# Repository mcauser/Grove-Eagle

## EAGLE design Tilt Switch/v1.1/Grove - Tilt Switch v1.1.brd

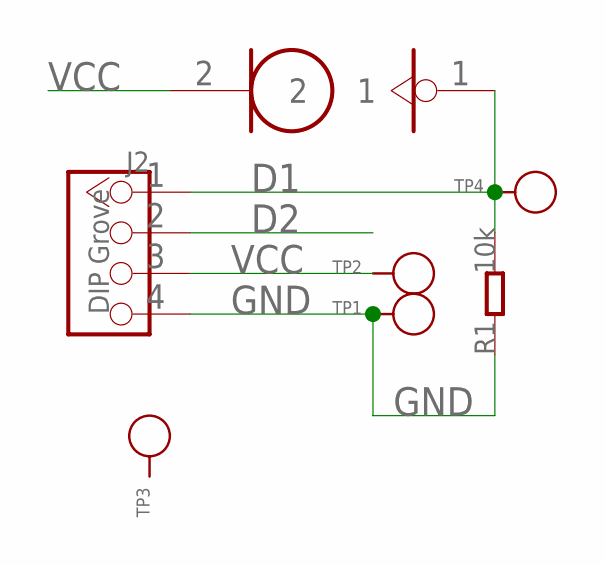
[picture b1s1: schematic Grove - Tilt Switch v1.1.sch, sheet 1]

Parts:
J1: TILT
J2: DIP Grove; 4P-2.0
R1: 10k; 0603
TP1, TP2, TP3, TP4: PAD-TEST-POINT'4545'; TP_4545

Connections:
D1: J1.1, J2.1, R1.2, TP4.T
D2: J2.2
GND: J2.4, R1.1, TP1.T
VCC: J1.2, J2.3, TP2.T

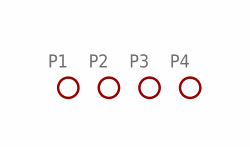
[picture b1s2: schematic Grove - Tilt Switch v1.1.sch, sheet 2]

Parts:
P1, P2, P3, P4: PAD-MARK; ROUND-MARK-1.0

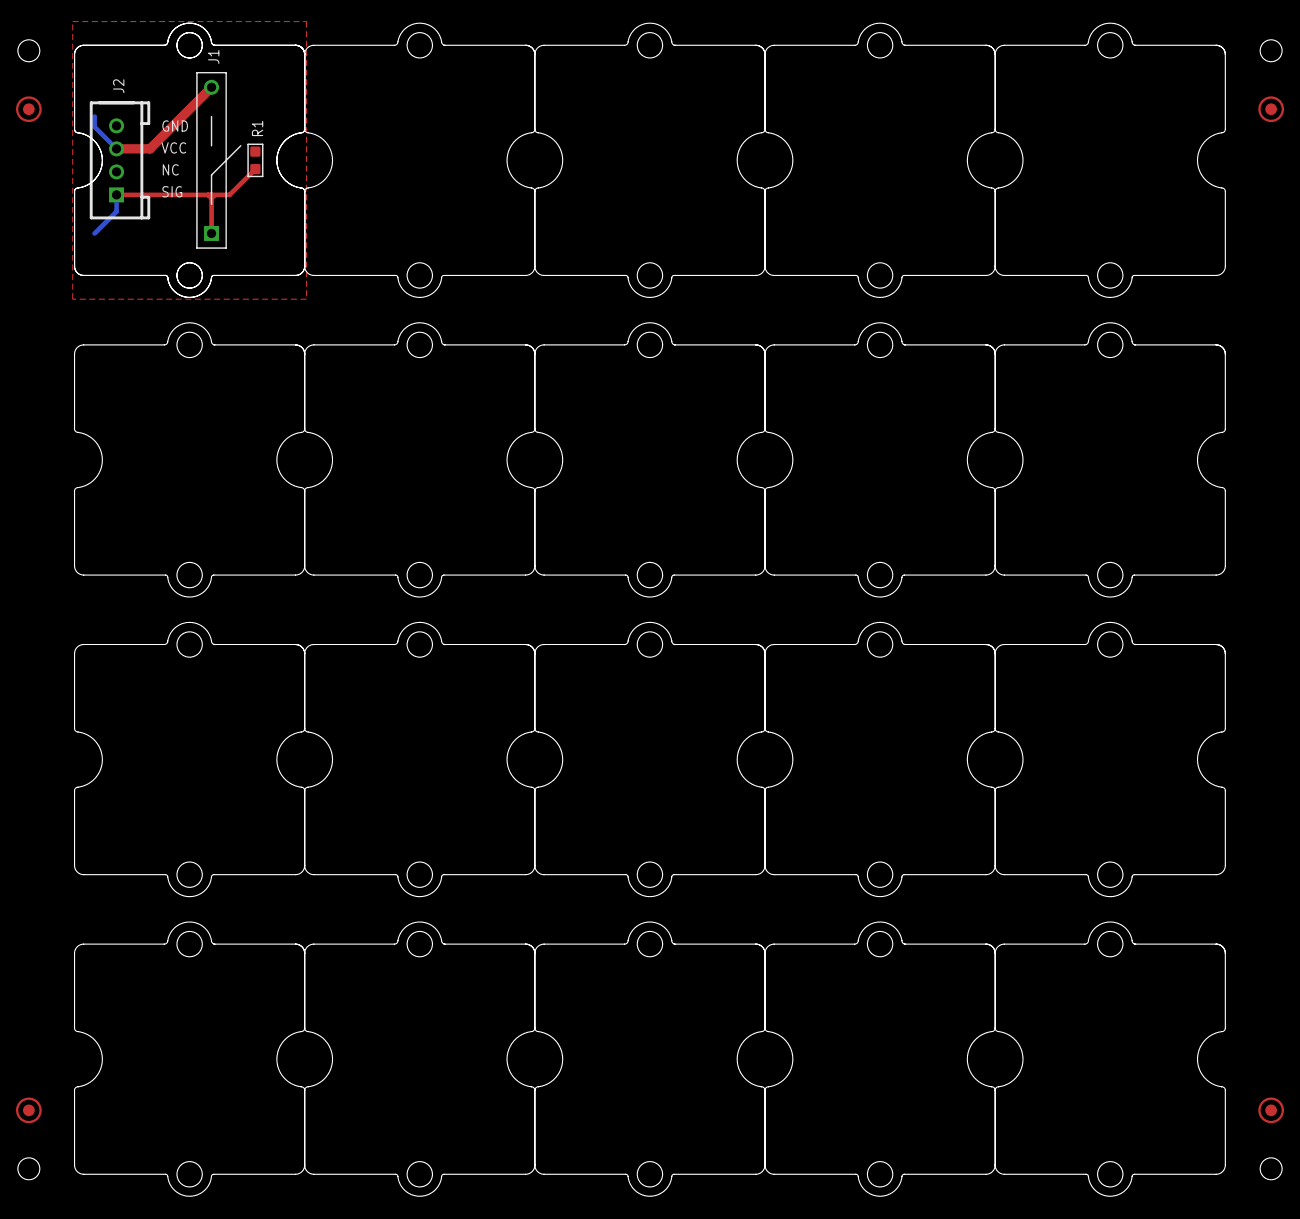
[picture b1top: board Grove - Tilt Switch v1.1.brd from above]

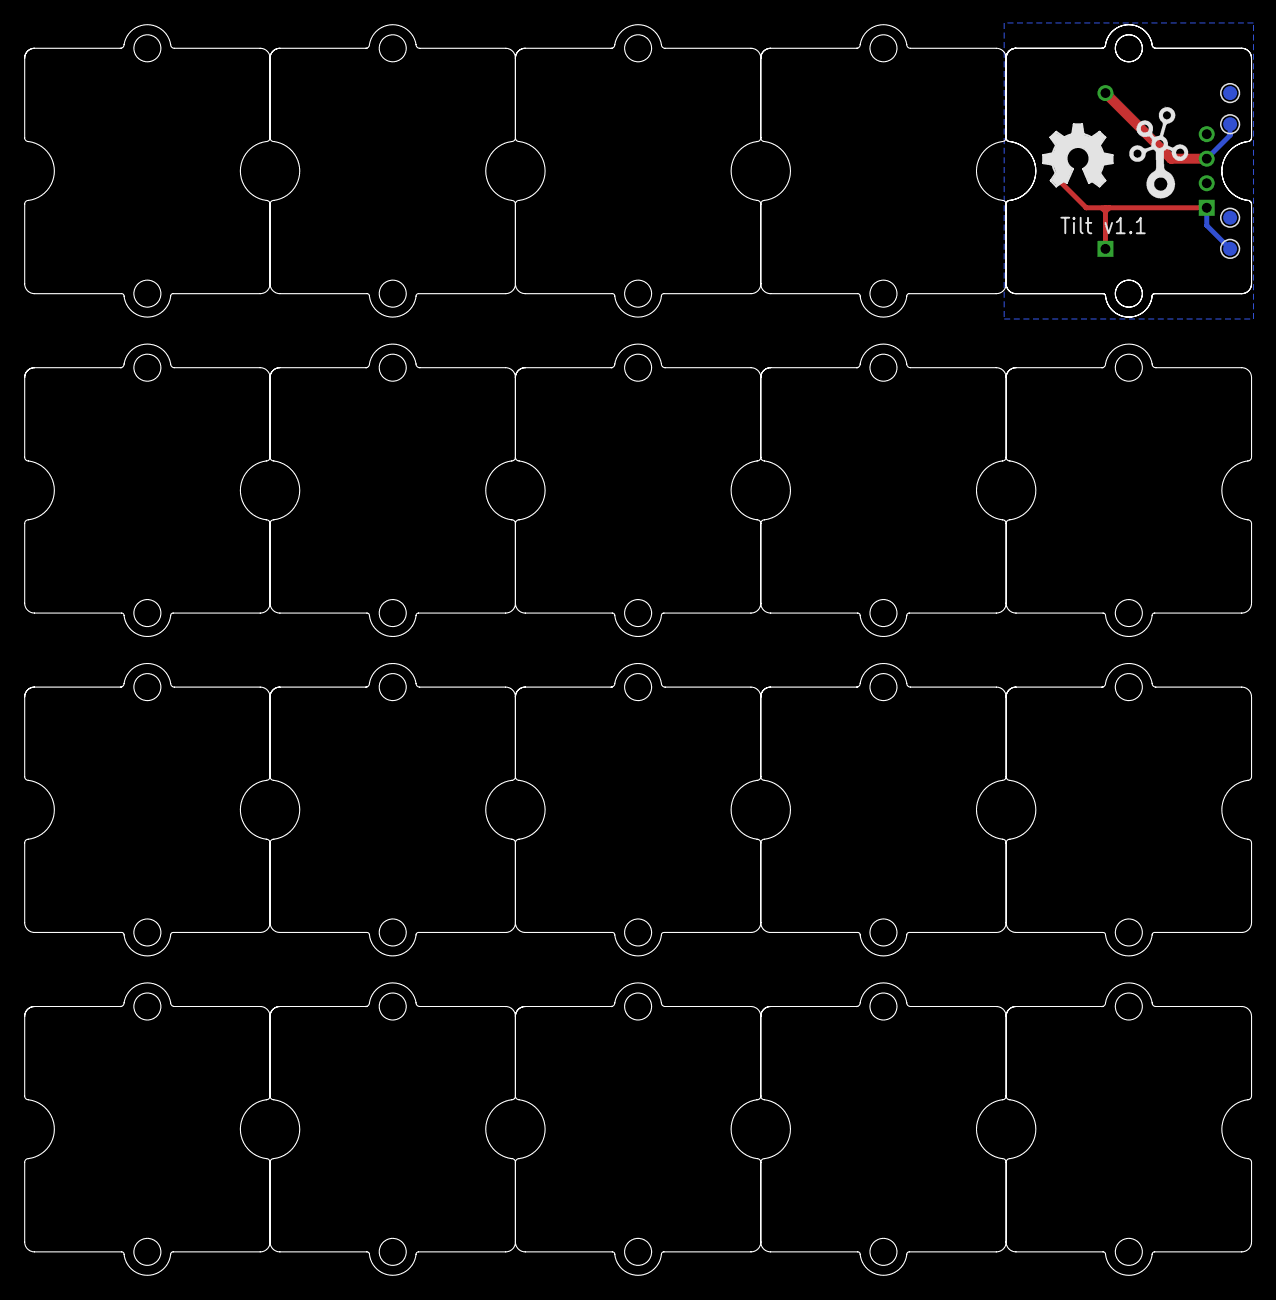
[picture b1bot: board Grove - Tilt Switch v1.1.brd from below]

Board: 2 copper layers, 100.0 x 101.9 mm, 34 parts (6 on the bottom side), 3 nets.

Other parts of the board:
U$2, U$6, U$7, U$8, U$9, U$10, U$11, U$12, U$13, U$14, U$15, U$16, U$17, U$18, U$19, U$20, U$21, U$22, U$23, U$24, U$25: 1U-DIM-W/-DRILL
U$3: OSHW_FILLX200_NOTEXT
U$5: TWIGLOGO

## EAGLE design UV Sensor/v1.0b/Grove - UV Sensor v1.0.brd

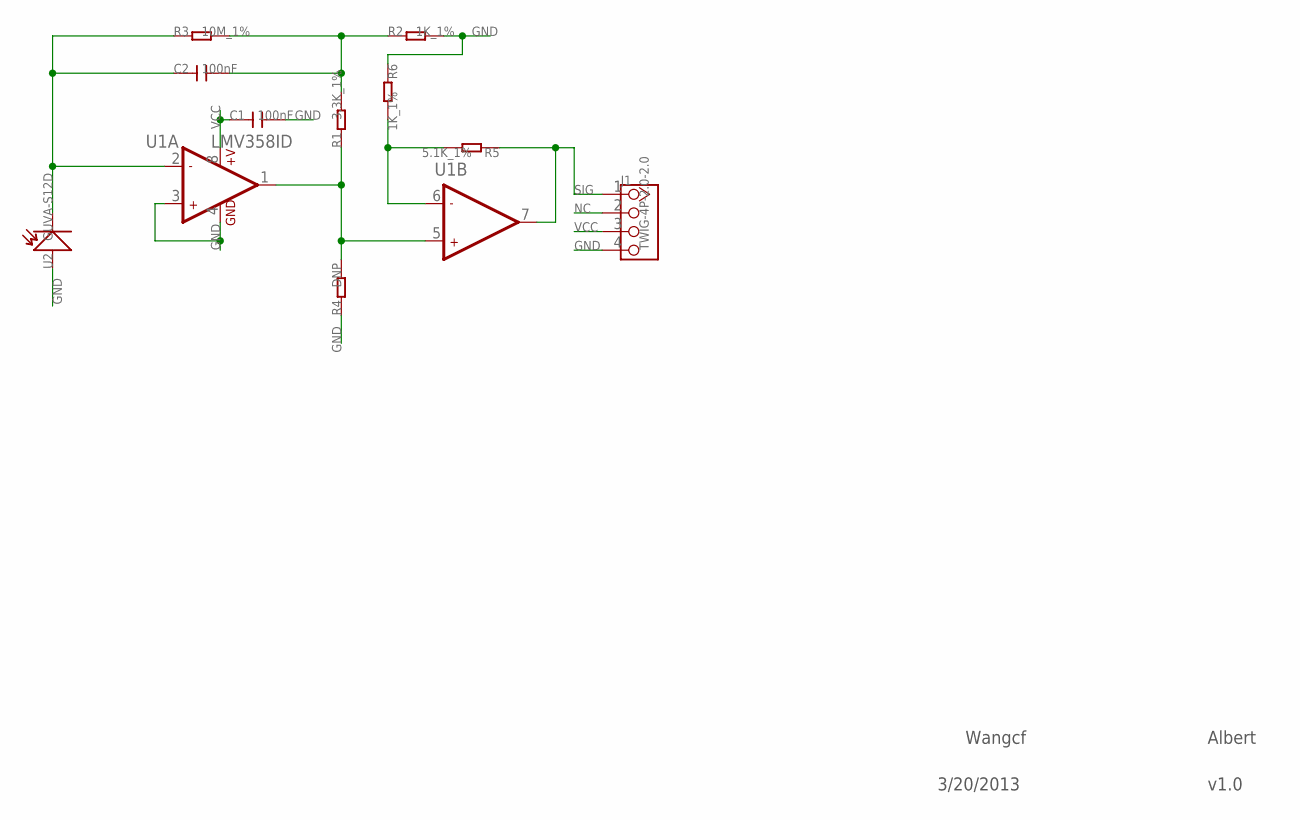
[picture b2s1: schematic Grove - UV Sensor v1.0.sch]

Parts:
C1, C2: 100nF; C0603
J1: TWIG-4P-2.0-2.0; 4P-2.0
R1: 3.3K_1%; R0603
R2, R6: 1K_1%; R0603
R3: 10M_1%; R0603
R4: DNP; R0603
R5: 5.1K_1%; R0603
U1: LMV358ID; SO08
U2: GUVA-S12D; LED-3528

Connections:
GND: C1.2, J1.4, R2.2, R4.1, R6.1, U1.3 (+IN1), U1.4 (GND), U2.1 (+)
unnamed: C2.1, R3.1, U1.2 (-IN1), U2.2 (-)
unnamed: R5.2, R6.2, U1.6 (-IN2)
unnamed: C2.2, R1.2, R2.1, R3.2
unnamed: J1.1, R5.1, U1.7 (OUT2)
NC: J1.2
SIG: R1.1, R4.2, U1.1 (OUT1), U1.5 (+IN2)
VCC: C1.1, J1.3, U1.8 (+V)

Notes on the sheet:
Wangcf
Albert
3/20/2013
v1.0

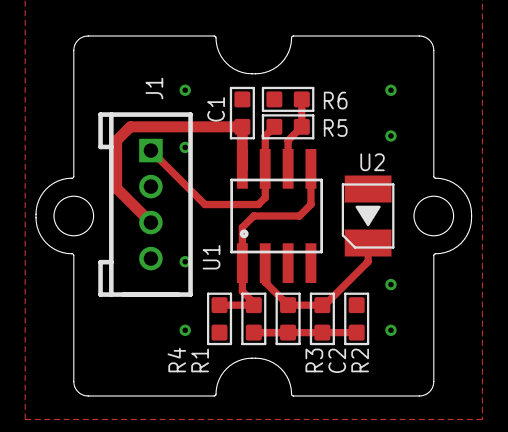
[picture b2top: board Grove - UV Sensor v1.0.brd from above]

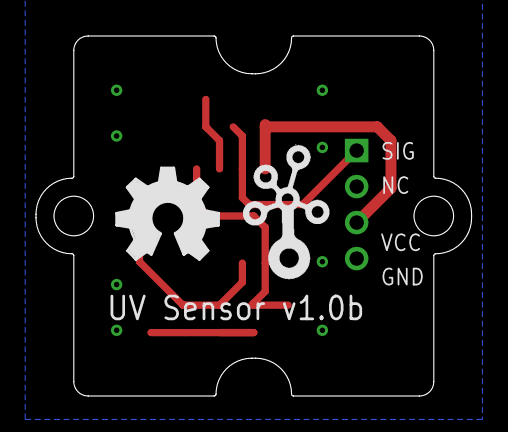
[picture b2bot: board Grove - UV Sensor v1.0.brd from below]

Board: 2 copper layers, 24.2 x 20.0 mm, 14 parts (2 on the bottom side), 7 nets.

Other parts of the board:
U$1: 1U-DIM-W/-DRILL
U$3: OSHW_FILLX200_NOTEXT
U$4: TWIGLOGO

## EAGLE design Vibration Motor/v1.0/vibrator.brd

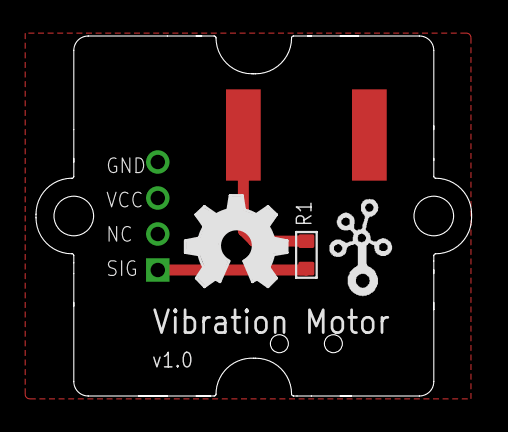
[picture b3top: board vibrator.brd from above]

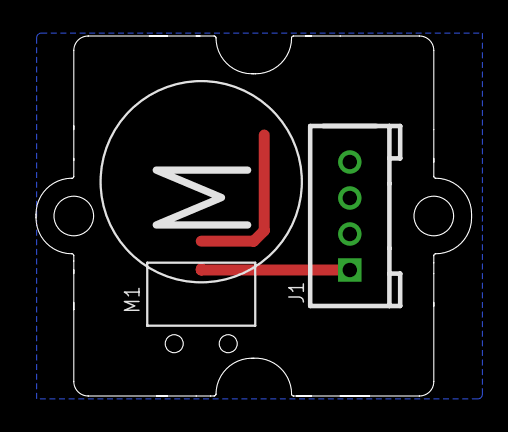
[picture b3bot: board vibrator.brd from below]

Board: 2 copper layers, 24.2 x 20.0 mm, 6 parts (3 on the bottom side), 3 nets.

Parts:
J1: TWIG_2.0-DIP-FEMALE; 2.0_1X4
M1: MOTOR_1CM
R1: 47R; 0603_S
TWIG1: U1N
U$1: TWIGLOGOTWIGLOGO_SMALL; TWIGLOGO_SMALL
U$2: OSHW_FILLX200_NOTEXT

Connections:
GND: J1.4, M1.2
unnamed: M1.1, R1.2
SIG: J1.1, R1.1

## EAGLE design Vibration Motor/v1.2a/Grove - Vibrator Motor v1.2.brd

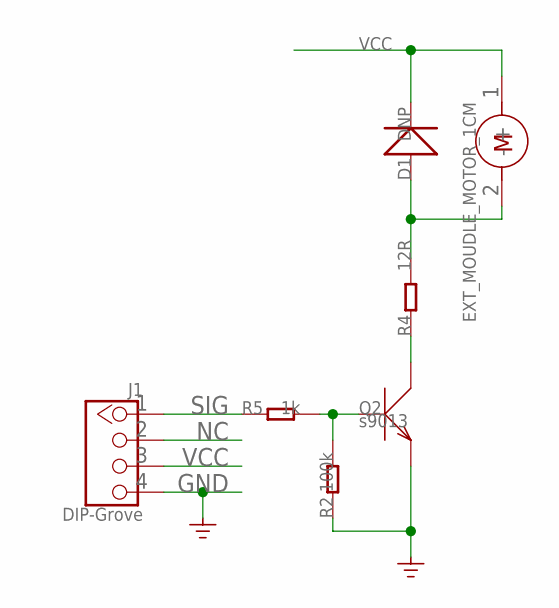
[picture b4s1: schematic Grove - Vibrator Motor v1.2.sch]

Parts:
D1: DNP; SOD123
J1: DIP-Grove; 2.0_1X4
M1: EXT_MOUDLE_MOTOR_1CM
Q2: s9013; SOT23
R2: 100k; R0603
R4: 12R; R0603
R5: 1k; R0603

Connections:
GND: J1.4, Q2.2 (E), R2.1
unnamed: D1.+, M1.2 (-), R4.2
unnamed: Q2.3 (C), R4.1
unnamed: Q2.1 (B), R2.2, R5.2
NC: J1.2
SIG: J1.1, R5.1
VCC: D1.-, J1.3, M1.1 (+)

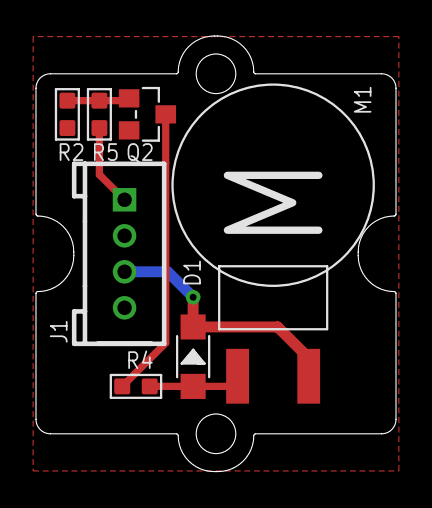
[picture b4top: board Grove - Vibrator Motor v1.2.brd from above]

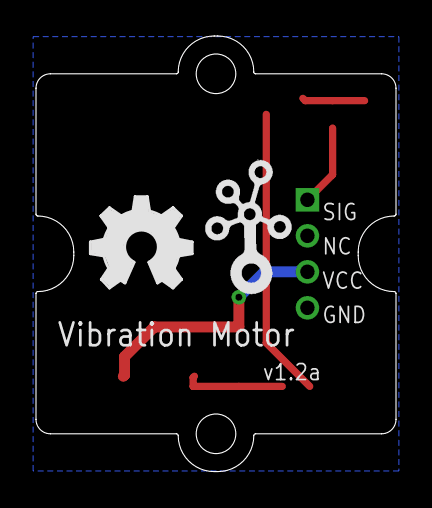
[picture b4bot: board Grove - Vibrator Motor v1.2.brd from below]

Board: 2 copper layers, 20.0 x 24.2 mm, 10 parts (2 on the bottom side), 6 nets.

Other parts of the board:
U$2: OSHW_FILLX200_NOTEXT
U$5: 1U-DIM-W/-DRILL
U$6: TWIGLOGO
